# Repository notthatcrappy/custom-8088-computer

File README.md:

# custom-8088-computer
Hello everybody, in this project i try to make my own 8088 computer, it is largely based on the FE-2010A chipset and the micro8088 project by @skiselev.

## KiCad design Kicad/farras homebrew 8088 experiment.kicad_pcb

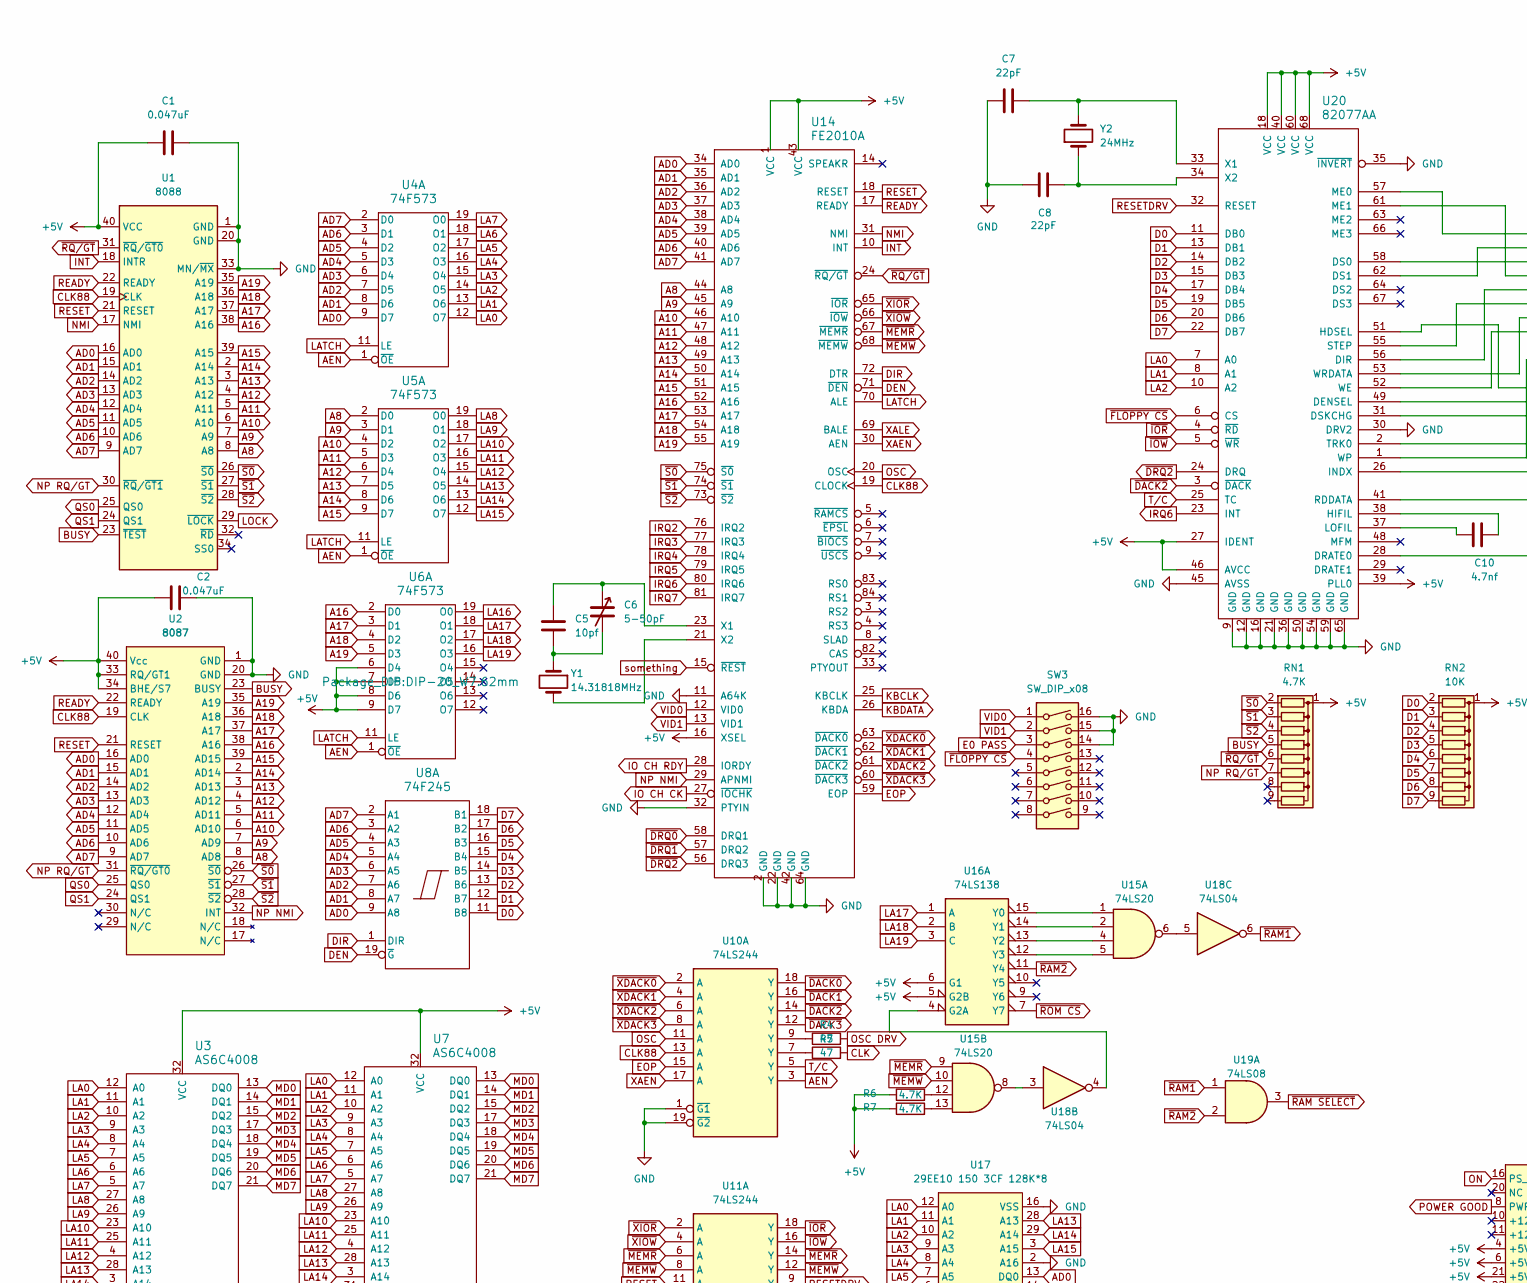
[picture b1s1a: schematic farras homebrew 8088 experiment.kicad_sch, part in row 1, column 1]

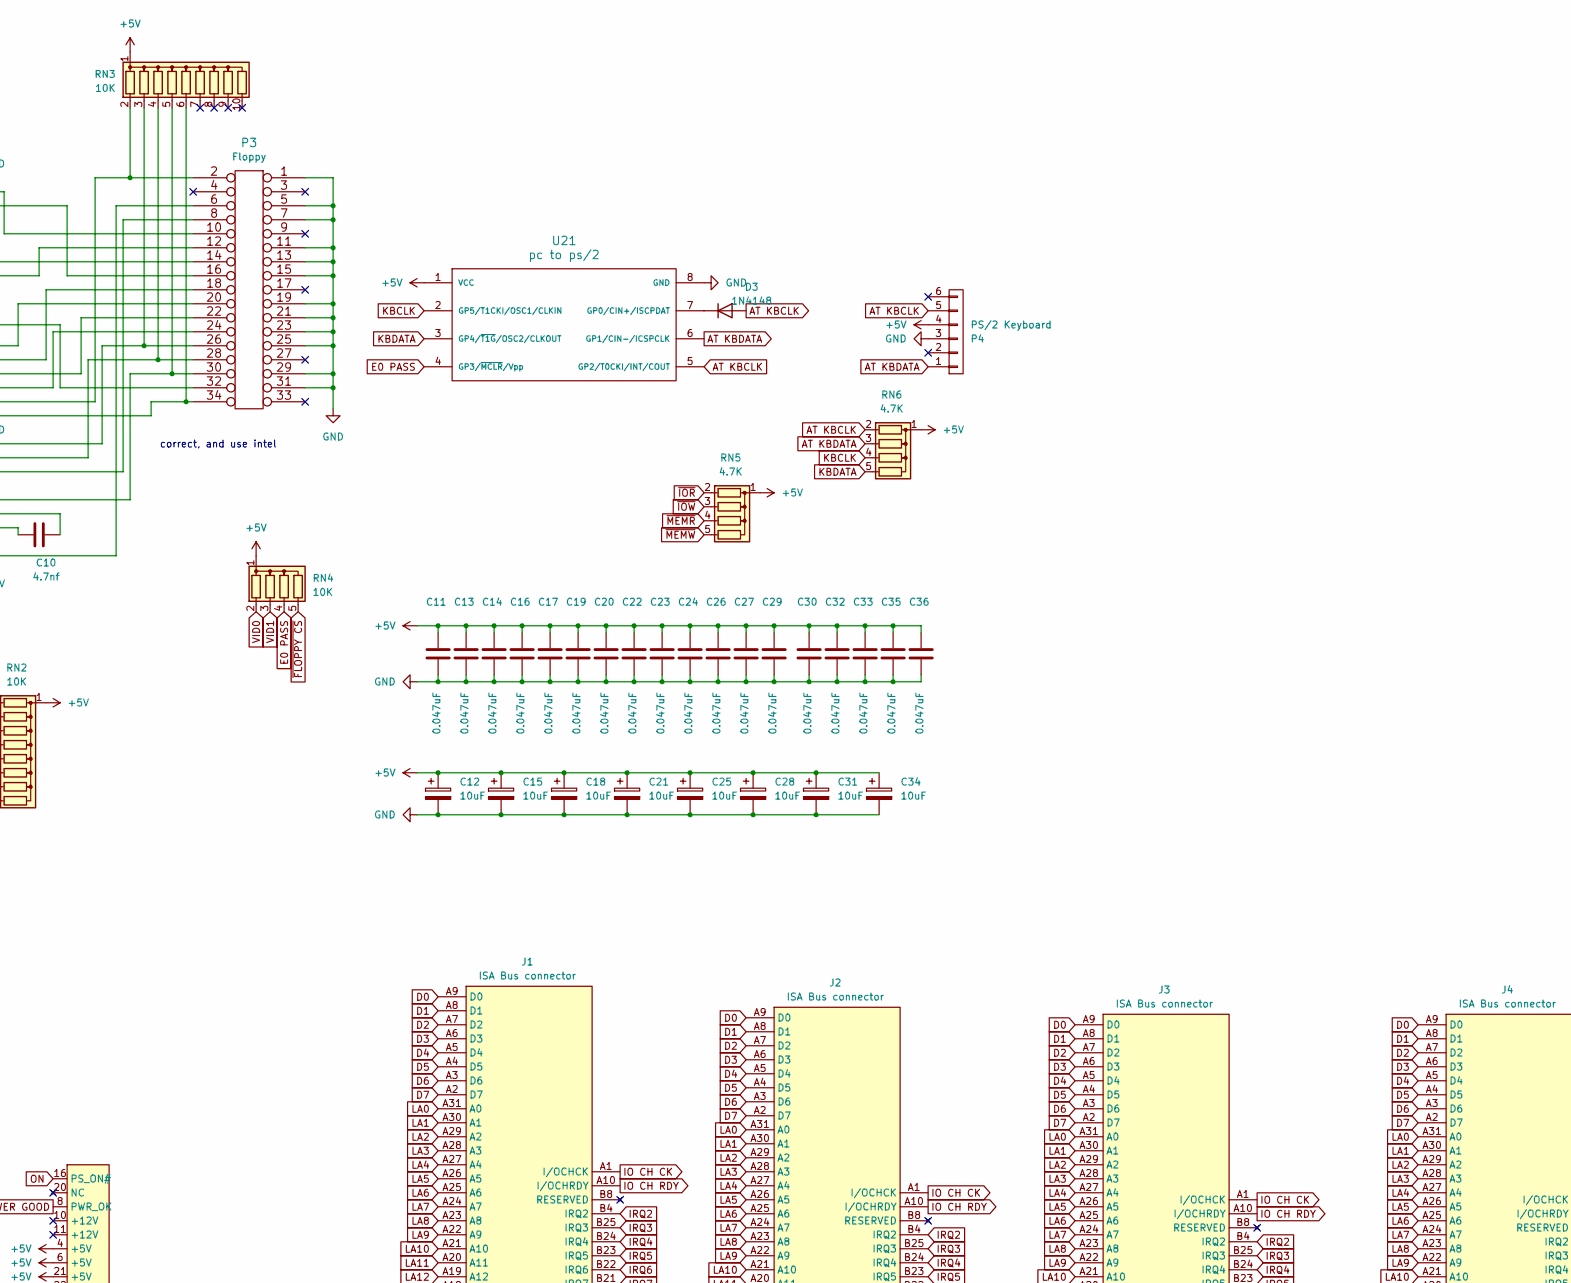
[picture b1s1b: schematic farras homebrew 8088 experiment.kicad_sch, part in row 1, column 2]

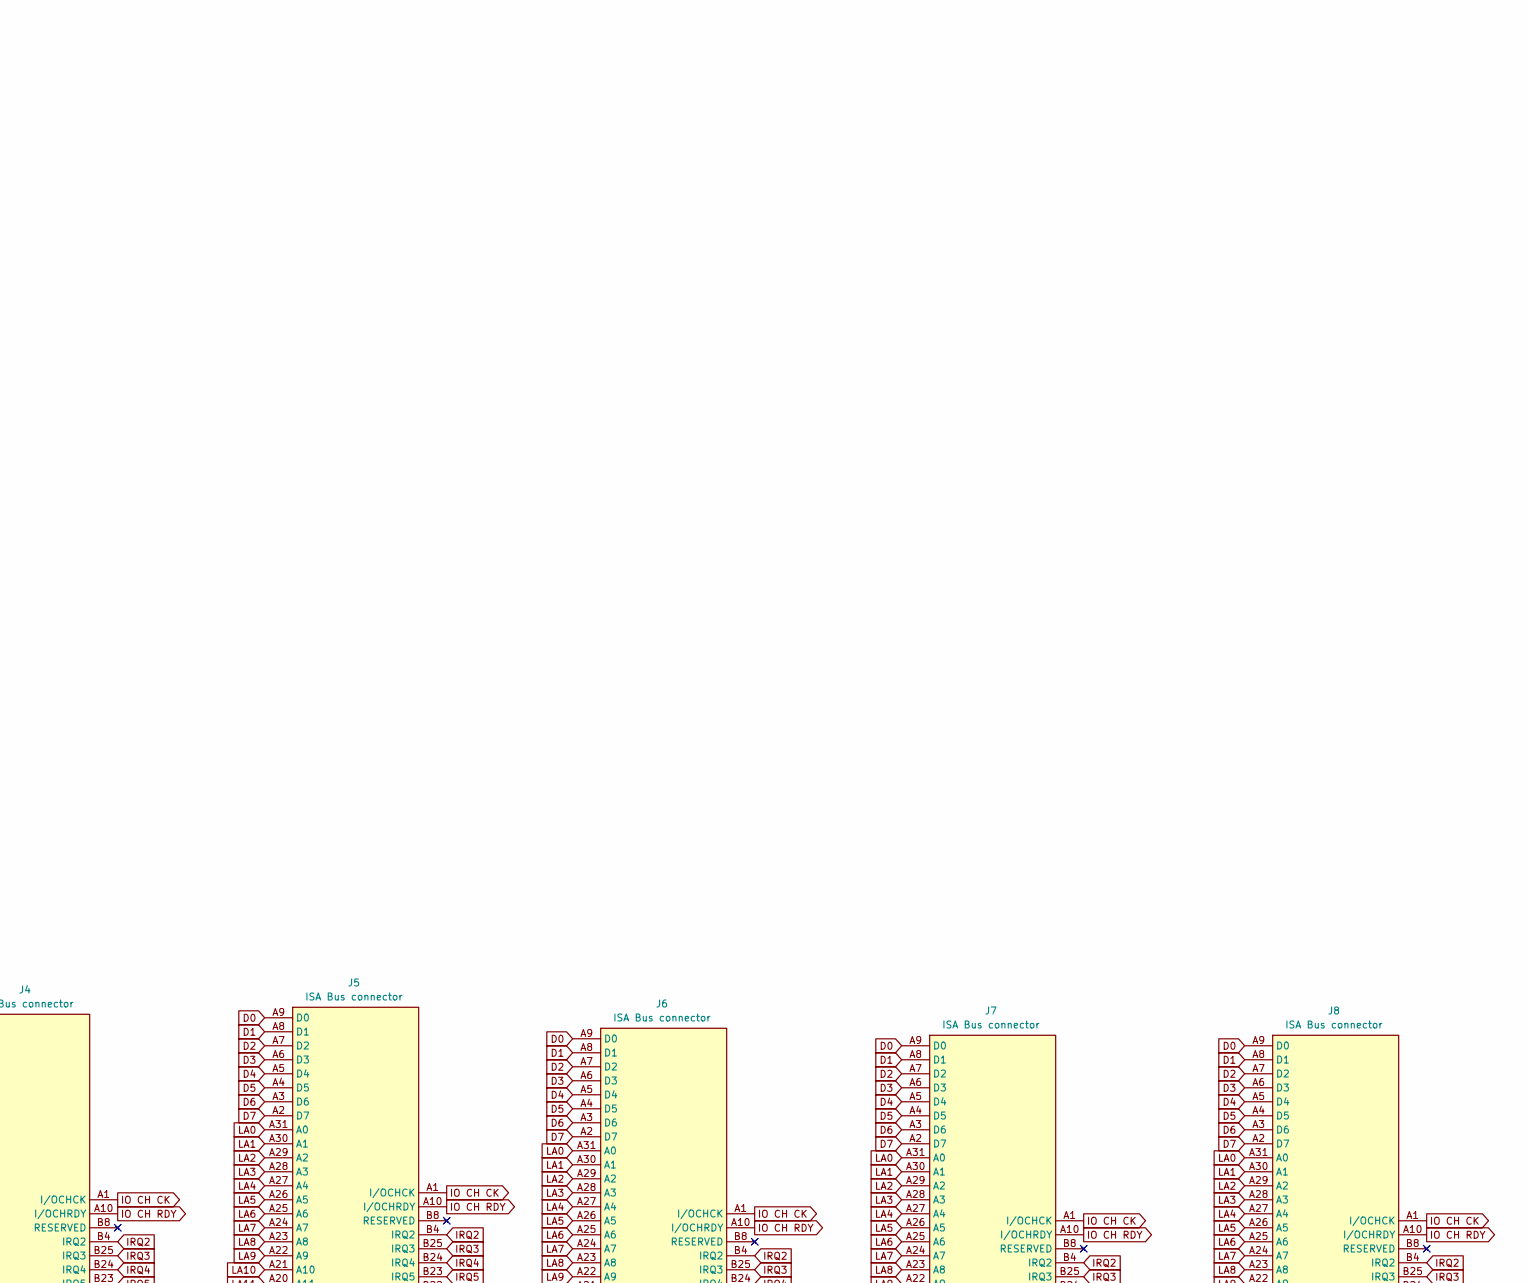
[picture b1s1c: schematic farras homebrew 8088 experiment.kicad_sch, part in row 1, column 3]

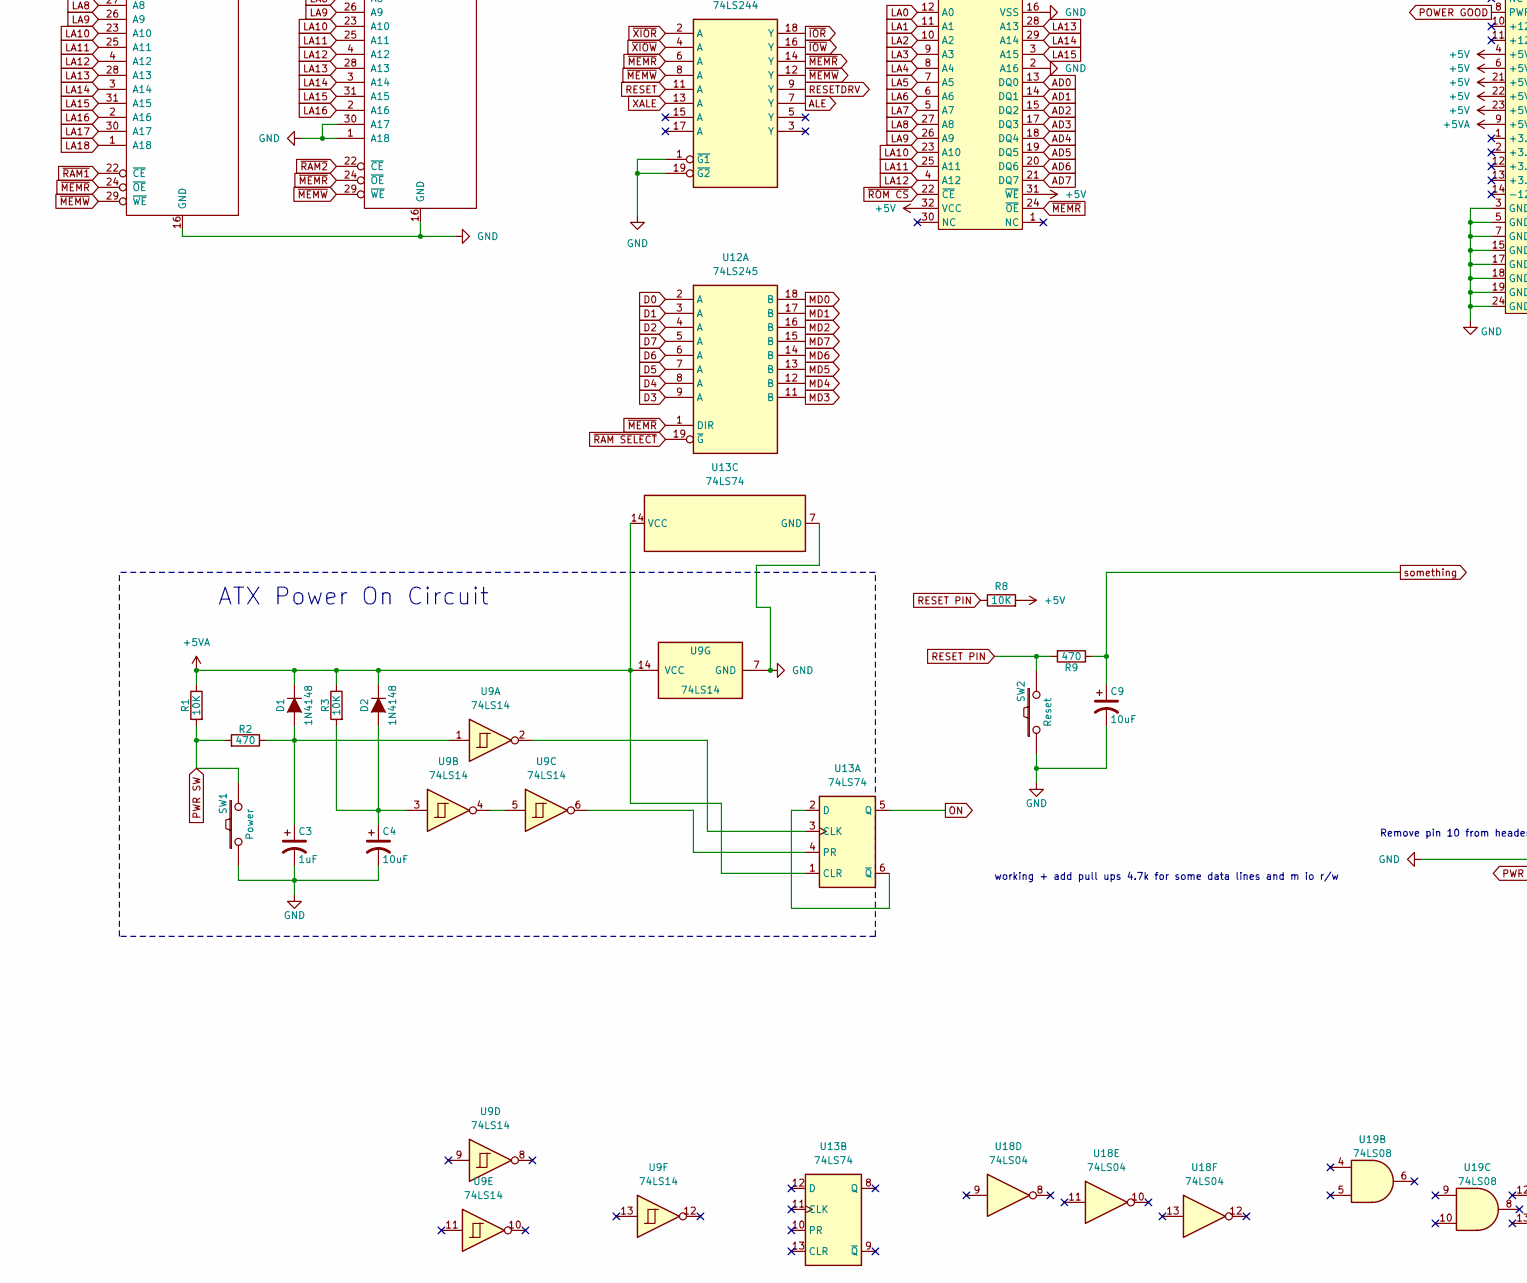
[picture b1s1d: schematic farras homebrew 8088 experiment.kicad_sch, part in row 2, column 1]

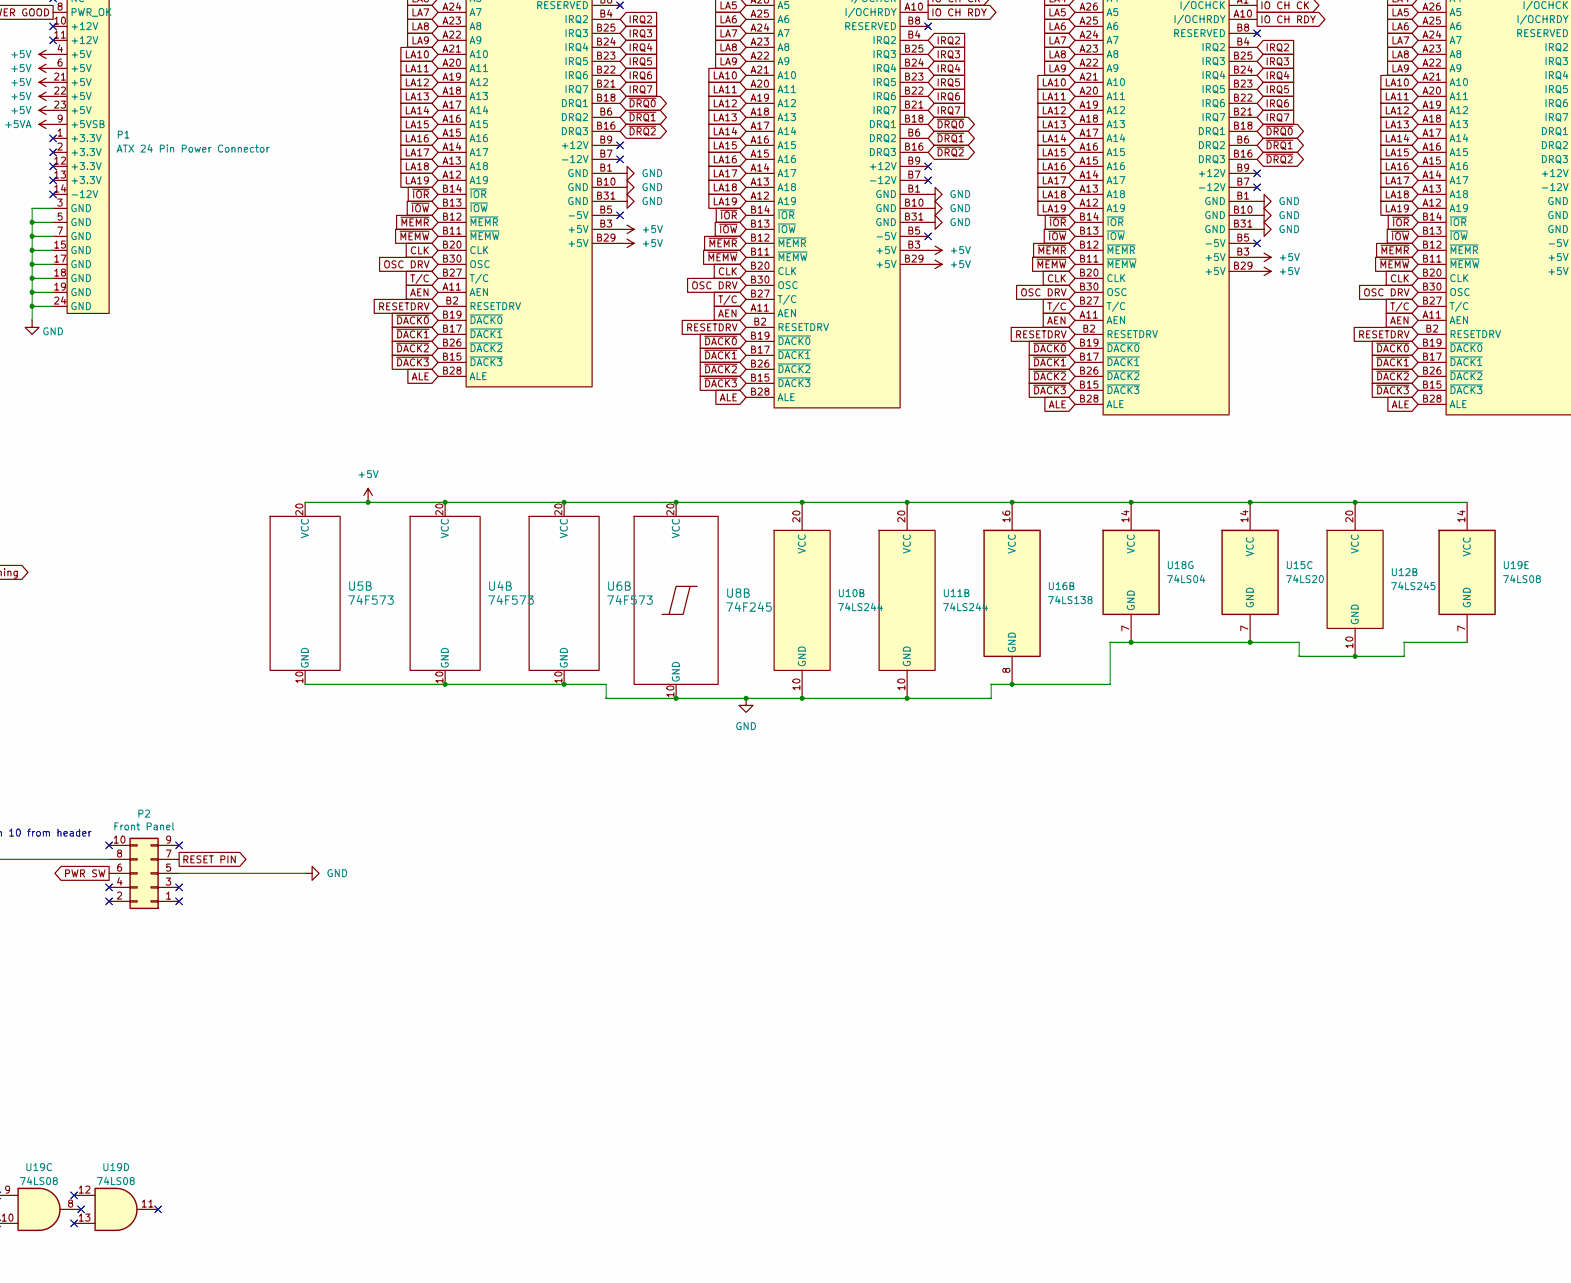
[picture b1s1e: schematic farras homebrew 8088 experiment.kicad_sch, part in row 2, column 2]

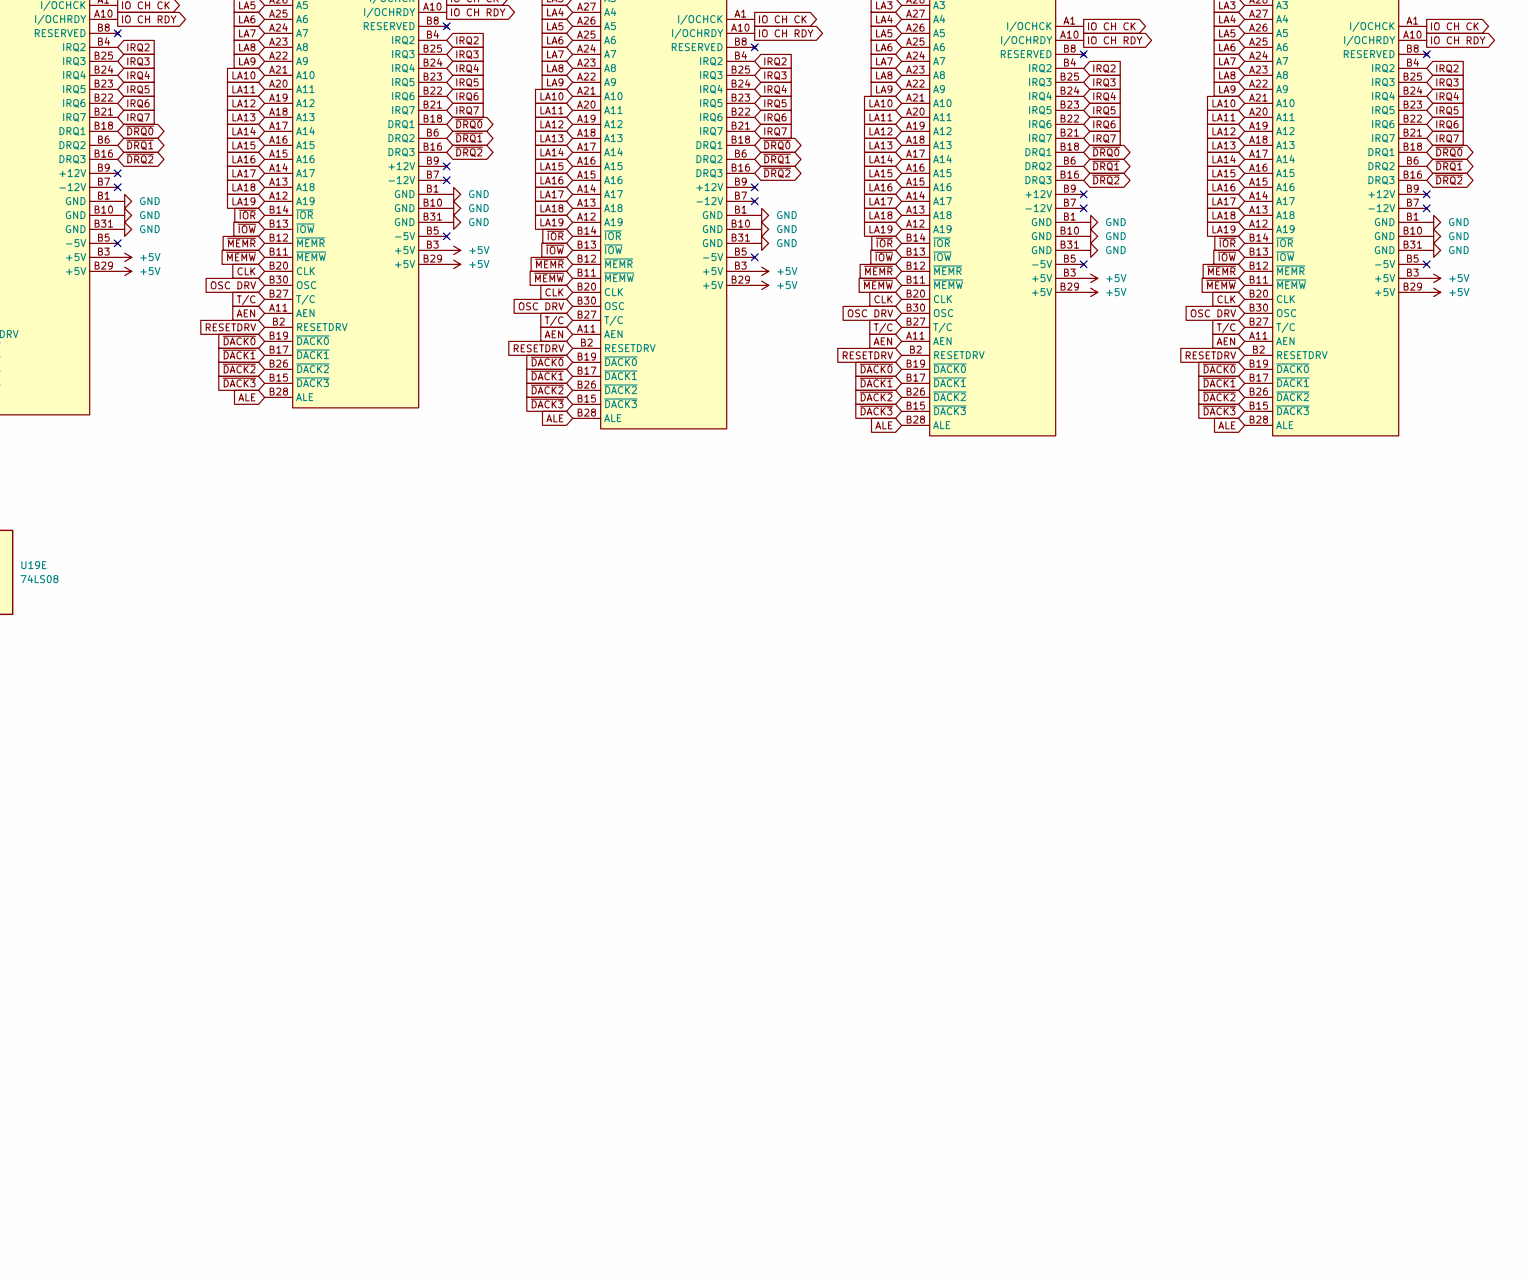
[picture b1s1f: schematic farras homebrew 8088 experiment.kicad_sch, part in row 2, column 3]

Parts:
C1, C2, C11, C13, C14, C16, C17, C19, C20, C22, C23, C24, C26, C27, C29, C30, C32, C33, C35, C36: 0.047uF; cap_unipolar
C3: 1uF; C_Disc_D4.3mm_W1.9mm_P5.00mm
C4, C9: 10uF; C_Disc_D4.3mm_W1.9mm_P5.00mm
C5: 10pf; cap_unipolar
C6: 5-50pF; trimmer cap
C7, C8: 22pF; cap_unipolar
C10: 4.7nf; cap_unipolar
C12, C15, C18, C21, C25, C28, C31, C34: 10uF; cap_tantalum_pos
D1, D2, D3: 1N4148; D_DO-34_SOD68_P7.62mm_Horizontal
J1, J2, J3, J4, J5, J6, J7, J8: ISA Bus connector; isa_edge_slot
P1: ATX 24 Pin Power Connector; Molex_Mini-Fit_Jr_5566-24A_2x12_P4.20mm_Vertical
P2: Front Panel; PinHeader_2x05_P2.54mm_Vertical
P3: Floppy; IDC-Header_2x17_P2.54mm_Vertical
P4: PS/2 Keyboard; Conn_Mini_DIN_6pin
R1, R3: 10K; R_Axial_DIN0207_L6.3mm_D2.5mm_P7.62mm_Horizontal
R2, R9: 470; R_Axial_DIN0207_L6.3mm_D2.5mm_P7.62mm_Horizontal
R4, R5: 47; resistor
R6, R7: 4.7K; resistor
R8: 10K; resistor
RN1: 4.7K; R_Array_SIP9
RN2: 10K; R_Array_SIP9
RN3: 10K; R_Array_SIP10
RN4: 10K; R_Array_SIP5
RN5, RN6: 4.7K; R_Array_SIP5
SW1: Power; SW_PUSH_6mm
SW2: Reset; SW_PUSH_6mm
SW3: SW_DIP_x08; SW_DIP_SPSTx08_Slide_9.78x22.5mm_W7.62mm_P2.54mm
U1: 8088; DIP-40_W15.24mm_Socket
U2: 8087; DIP-40_W15.24mm_Socket
U3, U7: AS6C4008; DIP-32_W15.24mm
U4, U5, U6: 74F573; DIP-20_W7.62mm
U8: 74F245; DIP-20_W7.62mm
U9: 74LS14; DIP-14_W7.62mm
U10, U11: 74LS244; DIP-20_W7.62mm
U12: 74LS245; DIP-20_W7.62mm
U13: 74LS74; DIP-14_W7.62mm_Socket
U14: FE2010A; PLCC-84_THT-Socket
U15: 74LS20; DIP-14_W7.62mm_Socket
U16: 74LS138; DIP-16_W7.62mm
U17: 29EE10 150 3CF 128K*8; DIP-32_W15.24mm_Socket
U18: 74LS04; DIP-14_W7.62mm_Socket
U19: 74LS08; DIP-14_W7.62mm_Socket
U20: 82077AA; PLCC-68_THT-Socket
U21: pc to ps/2; DIP-8_W7.62mm_Socket
Y1: 14.31818MHz; Crystal_HC49-U_Vertical
Y2: 24MHz; Crystal_HC49-U_Vertical

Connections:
+5V: C1.1, C2.1, C11.1, C12.1, C13.1, C14.1, C15.1, C16.1, C17.1, C18.1, C19.1, C20.1, C21.1, C22.1, C23.1, C24.1, C25.1, C26.1, C27.1, C28.1, C29.1, C30.1, C31.1, C32.1, C33.1, C34.1, C35.1, C36.1, J1.B3 (+5V), J1.B29 (+5V), J2.B3 (+5V), J2.B29 (+5V), J3.B3 (+5V), J3.B29 (+5V), J4.B3 (+5V), J4.B29 (+5V), J5.B3 (+5V), J5.B29 (+5V), J6.B3 (+5V), J6.B29 (+5V), J7.B3 (+5V), J7.B29 (+5V), J8.B3 (+5V), J8.B29 (+5V), P1.4 (+5V), P1.6 (+5V), P1.21 (+5V), P1.22 (+5V), P1.23 (+5V), P4.4, R6.1, R7.1, R8.2, RN1.1 (common), RN2.1 (common), RN3.1 (common), RN4.1 (common), RN5.1 (common), RN6.1 (common), U1.40 (VCC), U2.33 (RQ/GT1), U2.34 (BHE/S7), U2.40 (Vcc), U3.32 (VCC), U4.20 (VCC), U5.20 (VCC), U6.6 (D4), U6.7 (D5), U6.8 (D6), U6.9 (D7), U6.20 (VCC), U7.32 (VCC), U8.20 (VCC), U10.20 (VCC), U11.20 (VCC), U12.20 (VCC), U14.1 (VCC), U14.16 (XSEL), U14.43 (VCC), U15.14 (VCC), U16.5 (G2B), U16.6 (G1), U16.16 (VCC), U17.31 (~WE), U17.32 (VCC), U18.14 (VCC), U19.14 (VCC), U20.18 (VCC), U20.27 (IDENT), U20.39 (PLL0), U20.40 (VCC), U20.46 (AVCC), U20.60 (VCC), U20.68 (VCC), U21.1 (VCC)
+5VA: D1.1 (K), D2.1 (K), P1.9 (+5VSB), R1.1, R3.1, U9.14 (VCC), U13.1 (CLR), U13.14 (VCC)
-12V: P1.14 (-12V)
A8: U1.8 (A8), U2.8 (AD8), U5.2 (D0), U14.44 (A8)
A9: U1.7 (A9), U2.7 (AD9), U5.3 (D1), U14.45 (A9)
A10: U1.6 (A10), U2.6 (AD10), U5.4 (D2), U14.46 (A10)
A11: U1.5 (A11), U2.5 (AD11), U5.5 (D3), U14.47 (A11)
A12: U1.4 (A12), U2.4 (AD12), U5.6 (D4), U14.48 (A12)
A13: U1.3 (A13), U2.3 (AD13), U5.7 (D5), U14.49 (A13)
A14: U1.2 (A14), U2.2 (AD14), U5.8 (D6), U14.50 (A14)
A15: U1.39 (A15), U2.39 (AD15), U5.9 (D7), U14.51 (A15)
A16: U1.38 (A16), U2.38 (A16), U6.2 (D0), U14.52 (A16)
A17: U1.37 (A17), U2.37 (A17), U6.3 (D1), U14.53 (A17)
A18: U1.36 (A18), U2.36 (A18), U6.4 (D2), U14.54 (A18)
A19: U1.35 (A19), U2.35 (A19), U6.5 (D3), U14.55 (A19)
AD0: U1.16 (AD0), U2.16 (AD0), U4.9 (D7), U8.9 (A8), U14.34 (AD0), U17.13 (DQ0)
AD1: U1.15 (AD1), U2.15 (AD1), U4.8 (D6), U8.8 (A7), U14.35 (AD1), U17.14 (DQ1)
AD2: U1.14 (AD2), U2.14 (AD2), U4.7 (D5), U8.7 (A6), U14.36 (AD2), U17.15 (DQ2)
AD3: U1.13 (AD3), U2.13 (AD3), U4.6 (D4), U8.6 (A5), U14.37 (AD3), U17.17 (DQ3)
AD4: U1.12 (AD4), U2.12 (AD4), U4.5 (D3), U8.5 (A4), U14.38 (AD4), U17.18 (DQ4)
AD5: U1.11 (AD5), U2.11 (AD5), U4.4 (D2), U8.4 (A3), U14.39 (AD5), U17.19 (DQ5)
AD6: U1.10 (AD6), U2.10 (AD6), U4.3 (D1), U8.3 (A2), U14.40 (AD6), U17.20 (DQ6)
AD7: U1.9 (AD7), U2.9 (AD7), U4.2 (D0), U8.2 (A1), U14.41 (AD7), U17.21 (DQ7)
AEN: J1.A11 (AEN), J2.A11 (AEN), J3.A11 (AEN), J4.A11 (AEN), J5.A11 (AEN), J6.A11 (AEN), J7.A11 (AEN), J8.A11 (AEN), U4.1 (~OE), U5.1 (~OE), U6.1 (~OE), U10.3 (Y)
ALE: J1.B28 (ALE), J2.B28 (ALE), J3.B28 (ALE), J4.B28 (ALE), J5.B28 (ALE), J6.B28 (ALE), J7.B28 (ALE), J8.B28 (ALE), U11.7 (Y)
AT KBCLK: D3.2 (A), P4.5, RN6.2 (R1), U21.5 (GP2/T0CKI/INT/COUT)
AT KBDATA: P4.1, RN6.3 (R2), U21.6 (GP1/CIN-/ICSPCLK)
BUSY: RN1.5 (R4), U1.23 (~TEST), U2.23 (BUSY)
CLK: J1.B20 (CLK), J2.B20 (CLK), J3.B20 (CLK), J4.B20 (CLK), J5.B20 (CLK), J6.B20 (CLK), J7.B20 (CLK), J8.B20 (CLK), R5.2
CLK88: U1.19 (CLK), U2.19 (CLK), U10.13 (A), U14.19 (CLOCK)
D0: J1.A9 (D0), J2.A9 (D0), J3.A9 (D0), J4.A9 (D0), J5.A9 (D0), J6.A9 (D0), J7.A9 (D0), J8.A9 (D0), RN2.2 (R1), U8.11 (B8), U12.2 (A), U20.11 (DB0)
D1: J1.A8 (D1), J2.A8 (D1), J3.A8 (D1), J4.A8 (D1), J5.A8 (D1), J6.A8 (D1), J7.A8 (D1), J8.A8 (D1), RN2.3 (R2), U8.12 (B7), U12.3 (A), U20.13 (DB1)
D2: J1.A7 (D2), J2.A7 (D2), J3.A7 (D2), J4.A7 (D2), J5.A7 (D2), J6.A7 (D2), J7.A7 (D2), J8.A7 (D2), RN2.4 (R3), U8.13 (B6), U12.4 (A), U20.14 (DB2)
D3: J1.A6 (D3), J2.A6 (D3), J3.A6 (D3), J4.A6 (D3), J5.A6 (D3), J6.A6 (D3), J7.A6 (D3), J8.A6 (D3), RN2.5 (R4), U8.14 (B5), U12.9 (A), U20.15 (DB3)
D4: J1.A5 (D4), J2.A5 (D4), J3.A5 (D4), J4.A5 (D4), J5.A5 (D4), J6.A5 (D4), J7.A5 (D4), J8.A5 (D4), RN2.6 (R5), U8.15 (B4), U12.8 (A), U20.17 (DB4)
D5: J1.A4 (D5), J2.A4 (D5), J3.A4 (D5), J4.A4 (D5), J5.A4 (D5), J6.A4 (D5), J7.A4 (D5), J8.A4 (D5), RN2.7 (R6), U8.16 (B3), U12.7 (A), U20.19 (DB5)
D6: J1.A3 (D6), J2.A3 (D6), J3.A3 (D6), J4.A3 (D6), J5.A3 (D6), J6.A3 (D6), J7.A3 (D6), J8.A3 (D6), RN2.8 (R7), U8.17 (B2), U12.6 (A), U20.20 (DB6)
D7: J1.A2 (D7), J2.A2 (D7), J3.A2 (D7), J4.A2 (D7), J5.A2 (D7), J6.A2 (D7), J7.A2 (D7), J8.A2 (D7), RN2.9 (R8), U8.18 (B1), U12.5 (A), U20.22 (DB7)
DEN: U8.19 (~G), U14.71 (~DEN)
DIR: U8.1 (DIR), U14.72 (DTR)
E0 PASS: RN4.4 (R3), SW3.3, U21.4 (GP3/~MCLR/Vpp)
EOP: U10.15 (A), U14.59 (EOP)
GND: C1.2, C2.2, C3.2, C4.2, C7.1, C8.1, C9.2, C11.2, C12.2, C13.2, C14.2, C15.2, C16.2, C17.2, C18.2, C19.2, C20.2, C21.2, C22.2, C23.2, C24.2, C25.2, C26.2, C27.2, C28.2, C29.2, C30.2, C31.2, C32.2, C33.2, C34.2, C35.2, C36.2, J1.B1 (GND), J1.B10 (GND), J1.B31 (GND), J2.B1 (GND), J2.B10 (GND), J2.B31 (GND), J3.B1 (GND), J3.B10 (GND), J3.B31 (GND), J4.B1 (GND), J4.B10 (GND), J4.B31 (GND), J5.B1 (GND), J5.B10 (GND), J5.B31 (GND), J6.B1 (GND), J6.B10 (GND), J6.B31 (GND), J7.B1 (GND), J7.B10 (GND), J7.B31 (GND), J8.B1 (GND), J8.B10 (GND), J8.B31 (GND), P1.3 (GND), P1.5 (GND), P1.7 (GND), P1.15 (GND), P1.17 (GND), P1.18 (GND), P1.19 (GND), P1.24 (GND), P2.5, P2.8, P3.1, P3.5, P3.7, P3.11, P3.13, P3.15, P3.19, P3.21, P3.23, P3.25, P3.29, P3.31, P4.3, SW1.1, SW2.1, SW3.14, SW3.15, SW3.16, U1.1 (GND), U1.20 (GND), U1.33 (MN/~MX), U2.1 (GND), U2.20 (GND), U3.16 (GND), U4.10 (GND), U5.10 (GND), U6.10 (GND), U7.1 (A18), U7.16 (GND), U7.30 (A17), U8.10 (GND), U9.7 (GND), U10.1 (~G1), U10.10 (GND), U10.19 (~G2), U11.1 (~G1), U11.10 (GND), U11.19 (~G2), U12.10 (GND), U13.7 (GND), U14.2 (GND), U14.11 (A64K), U14.22 (GND), U14.32 (PTYIN), U14.42 (GND), U14.64 (GND)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
INT: U1.18 (INTR), U14.10 (INT)
IO CH CK: J1.A1 (I/OCHCK), J2.A1 (I/OCHCK), J3.A1 (I/OCHCK), J4.A1 (I/OCHCK), J5.A1 (I/OCHCK), J6.A1 (I/OCHCK), J7.A1 (I/OCHCK), J8.A1 (I/OCHCK), U14.27 (~IOCHK)
IO CH RDY: J1.A10 (I/OCHRDY), J2.A10 (I/OCHRDY), J3.A10 (I/OCHRDY), J4.A10 (I/OCHRDY), J5.A10 (I/OCHRDY), J6.A10 (I/OCHRDY), J7.A10 (I/OCHRDY), J8.A10 (I/OCHRDY), U14.28 (IORDY)
IRQ2: J1.B4 (IRQ2), J2.B4 (IRQ2), J3.B4 (IRQ2), J4.B4 (IRQ2), J5.B4 (IRQ2), J6.B4 (IRQ2), J7.B4 (IRQ2), J8.B4 (IRQ2), U14.76 (IRQ2)
IRQ3: J1.B25 (IRQ3), J2.B25 (IRQ3), J3.B25 (IRQ3), J4.B25 (IRQ3), J5.B25 (IRQ3), J6.B25 (IRQ3), J7.B25 (IRQ3), J8.B25 (IRQ3), U14.77 (IRQ3)
IRQ4: J1.B24 (IRQ4), J2.B24 (IRQ4), J3.B24 (IRQ4), J4.B24 (IRQ4), J5.B24 (IRQ4), J6.B24 (IRQ4), J7.B24 (IRQ4), J8.B24 (IRQ4), U14.78 (IRQ4)
IRQ5: J1.B23 (IRQ5), J2.B23 (IRQ5), J3.B23 (IRQ5), J4.B23 (IRQ5), J5.B23 (IRQ5), J6.B23 (IRQ5), J7.B23 (IRQ5), J8.B23 (IRQ5), U14.79 (IRQ5)
IRQ6: J1.B22 (IRQ6), J2.B22 (IRQ6), J3.B22 (IRQ6), J4.B22 (IRQ6), J5.B22 (IRQ6), J6.B22 (IRQ6), J7.B22 (IRQ6), J8.B22 (IRQ6), U14.80 (IRQ6), U20.23 (INT)
IRQ7: J1.B21 (IRQ7), J2.B21 (IRQ7), J3.B21 (IRQ7), J4.B21 (IRQ7), J5.B21 (IRQ7), J6.B21 (IRQ7), J7.B21 (IRQ7), J8.B21 (IRQ7), U14.81 (IRQ7)
KBCLK: RN6.4 (R3), U14.25 (KBCLK), U21.2 (GP5/T1CKI/OSC1/CLKIN)
KBDATA: RN6.5 (R4), U14.26 (KBDA), U21.3 (GP4/~T1G/OSC2/CLKOUT)
LA0: J1.A31 (A0), J2.A31 (A0), J3.A31 (A0), J4.A31 (A0), J5.A31 (A0), J6.A31 (A0), J7.A31 (A0), J8.A31 (A0), U3.12 (A0), U4.12 (O7), U7.12 (A0), U17.12 (A0), U20.7 (A0)
LA1: J1.A30 (A1), J2.A30 (A1), J3.A30 (A1), J4.A30 (A1), J5.A30 (A1), J6.A30 (A1), J7.A30 (A1), J8.A30 (A1), U3.11 (A1), U4.13 (O6), U7.11 (A1), U17.11 (A1), U20.8 (A1)
LA2: J1.A29 (A2), J2.A29 (A2), J3.A29 (A2), J4.A29 (A2), J5.A29 (A2), J6.A29 (A2), J7.A29 (A2), J8.A29 (A2), U3.10 (A2), U4.14 (O5), U7.10 (A2), U17.10 (A2), U20.10 (A2)
LA3: J1.A28 (A3), J2.A28 (A3), J3.A28 (A3), J4.A28 (A3), J5.A28 (A3), J6.A28 (A3), J7.A28 (A3), J8.A28 (A3), U3.9 (A3), U4.15 (O4), U7.9 (A3), U17.9 (A3)
LA4: J1.A27 (A4), J2.A27 (A4), J3.A27 (A4), J4.A27 (A4), J5.A27 (A4), J6.A27 (A4), J7.A27 (A4), J8.A27 (A4), U3.8 (A4), U4.16 (O3), U7.8 (A4), U17.8 (A4)
LA5: J1.A26 (A5), J2.A26 (A5), J3.A26 (A5), J4.A26 (A5), J5.A26 (A5), J6.A26 (A5), J7.A26 (A5), J8.A26 (A5), U3.7 (A5), U4.17 (O2), U7.7 (A5), U17.7 (A5)
LA6: J1.A25 (A6), J2.A25 (A6), J3.A25 (A6), J4.A25 (A6), J5.A25 (A6), J6.A25 (A6), J7.A25 (A6), J8.A25 (A6), U3.6 (A6), U4.18 (O1), U7.6 (A6), U17.6 (A6)
LA7: J1.A24 (A7), J2.A24 (A7), J3.A24 (A7), J4.A24 (A7), J5.A24 (A7), J6.A24 (A7), J7.A24 (A7), J8.A24 (A7), U3.5 (A7), U4.19 (O0), U7.5 (A7), U17.5 (A7)
LA8: J1.A23 (A8), J2.A23 (A8), J3.A23 (A8), J4.A23 (A8), J5.A23 (A8), J6.A23 (A8), J7.A23 (A8), J8.A23 (A8), U3.27 (A8), U5.19 (O0), U7.27 (A8), U17.27 (A8)
LA9: J1.A22 (A9), J2.A22 (A9), J3.A22 (A9), J4.A22 (A9), J5.A22 (A9), J6.A22 (A9), J7.A22 (A9), J8.A22 (A9), U3.26 (A9), U5.18 (O1), U7.26 (A9), U17.26 (A9)
LA10: J1.A21 (A10), J2.A21 (A10), J3.A21 (A10), J4.A21 (A10), J5.A21 (A10), J6.A21 (A10), J7.A21 (A10), J8.A21 (A10), U3.23 (A10), U5.17 (O2), U7.23 (A10), U17.23 (A10)
LA11: J1.A20 (A11), J2.A20 (A11), J3.A20 (A11), J4.A20 (A11), J5.A20 (A11), J6.A20 (A11), J7.A20 (A11), J8.A20 (A11), U3.25 (A11), U5.16 (O3), U7.25 (A11), U17.25 (A11)
LA12: J1.A19 (A12), J2.A19 (A12), J3.A19 (A12), J4.A19 (A12), J5.A19 (A12), J6.A19 (A12), J7.A19 (A12), J8.A19 (A12), U3.4 (A12), U5.15 (O4), U7.4 (A12), U17.4 (A12)
LA13: J1.A18 (A13), J2.A18 (A13), J3.A18 (A13), J4.A18 (A13), J5.A18 (A13), J6.A18 (A13), J7.A18 (A13), J8.A18 (A13), U3.28 (A13), U5.14 (O5), U7.28 (A13), U17.28 (A13)
LA14: J1.A17 (A14), J2.A17 (A14), J3.A17 (A14), J4.A17 (A14), J5.A17 (A14), J6.A17 (A14), J7.A17 (A14), J8.A17 (A14), U3.3 (A14), U5.13 (O6), U7.3 (A14), U17.29 (A14)
LA15: J1.A16 (A15), J2.A16 (A15), J3.A16 (A15), J4.A16 (A15), J5.A16 (A15), J6.A16 (A15), J7.A16 (A15), J8.A16 (A15), U3.31 (A15), U5.12 (O7), U7.31 (A15), U17.3 (A15)
LA16: J1.A15 (A16), J2.A15 (A16), J3.A15 (A16), J4.A15 (A16), J5.A15 (A16), J6.A15 (A16), J7.A15 (A16), J8.A15 (A16), U3.2 (A16), U6.19 (O0), U7.2 (A16)
LA17: J1.A14 (A17), J2.A14 (A17), J3.A14 (A17), J4.A14 (A17), J5.A14 (A17), J6.A14 (A17), J7.A14 (A17), J8.A14 (A17), U3.30 (A17), U6.18 (O1), U16.1 (A)
LA18: J1.A13 (A18), J2.A13 (A18), J3.A13 (A18), J4.A13 (A18), J5.A13 (A18), J6.A13 (A18), J7.A13 (A18), J8.A13 (A18), U3.1 (A18), U6.17 (O2), U16.2 (B)
LA19: J1.A12 (A19), J2.A12 (A19), J3.A12 (A19), J4.A12 (A19), J5.A12 (A19), J6.A12 (A19), J7.A12 (A19), J8.A12 (A19), U6.16 (O3), U16.3 (C)
LATCH: U4.11 (LE), U5.11 (LE), U6.11 (LE), U14.70 (ALE)
LOCK: U1.29 (~LOCK)
MD0: U3.13 (DQ0), U7.13 (DQ0), U12.18 (B)
MD1: U3.14 (DQ1), U7.14 (DQ1), U12.17 (B)
MD2: U3.15 (DQ2), U7.15 (DQ2), U12.16 (B)
MD3: U3.17 (DQ3), U7.17 (DQ3), U12.11 (B)
MD4: U3.18 (DQ4), U7.18 (DQ4), U12.12 (B)
MD5: U3.19 (DQ5), U7.19 (DQ5), U12.13 (B)
MD6: U3.20 (DQ6), U7.20 (DQ6), U12.14 (B)
MD7: U3.21 (DQ7), U7.21 (DQ7), U12.15 (B)
NMI: U1.17 (NMI), U14.31 (NMI)
NP NMI: U2.32 (INT), U14.29 (APNMI)
NP RQ/GT: RN1.7 (R6), U1.30 (~RQ/~GT1), U2.31 (~RQ/GT0)
unnamed: C5.2, C6.2, Y1.1
unnamed: C3.1, D1.2 (A), R2.1, U9.1
unnamed: C4.1, D2.2 (A), R3.2, U9.3
unnamed: D3.1 (K), U21.7 (GP0/CIN+/ISCPDAT)
unnamed: P3.2, RN3.2 (R1), U20.49 (DENSEL)
unnamed: P3.6, U20.28 (DRATE0)
unnamed: P3.8, U20.26 (INDX)
unnamed: P3.10, U20.57 (ME0)
unnamed: P3.12, U20.62 (DS1)
unnamed: P3.14, U20.58 (DS0)
unnamed: P3.16, U20.61 (ME1)
unnamed: P3.18, U20.56 (DIR)
unnamed: P3.20, U20.55 (STEP)
unnamed: P3.22, U20.53 (WRDATA)
unnamed: P3.24, U20.52 (WE)
unnamed: P3.26, RN3.3 (R2), U20.2 (TRK0)
unnamed: P3.28, RN3.4 (R3), U20.1 (WP)
unnamed: P3.30, RN3.5 (R4), U20.41 (RDDATA)
unnamed: P3.32, U20.51 (HDSEL)
unnamed: P3.34, RN3.6 (R5), U20.31 (DSKCHG)
unnamed: R4.1, U10.9 (Y)
unnamed: R5.1, U10.7 (Y)
unnamed: R6.2, U15.12
unnamed: R7.2, U15.13
unnamed: U9.4, U9.5
unnamed: U9.2, U13.3 (CLK)
unnamed: U13.2 (D), U13.6 (~Q)
unnamed: U9.6, U13.4 (PR)
unnamed: C5.1, C6.1, U14.23 (X1)
unnamed: U14.21 (X2), Y1.2
unnamed: U15.6, U18.5
unnamed: U15.8, U18.3
unnamed: U16.4 (G2A), U18.4
unnamed: U15.1, U16.15 (Y0)
unnamed: U15.2, U16.14 (Y1)
unnamed: U15.4, U16.13 (Y2)
unnamed: U15.5, U16.12 (Y3)
unnamed: C10.2, U20.38 (HIFIL)
unnamed: C10.1, U20.37 (LOFIL)
unnamed: C7.2, U20.33 (X1), Y2.2
unnamed: C8.2, U20.34 (X2), Y2.1
ON: P1.16 (PS_ON#), U13.5 (Q)
OSC: U10.11 (A), U14.20 (OSC)
OSC DRV: J1.B30 (OSC), J2.B30 (OSC), J3.B30 (OSC), J4.B30 (OSC), J5.B30 (OSC), J6.B30 (OSC), J7.B30 (OSC), J8.B30 (OSC), R4.2
POWER GOOD: P1.8 (PWR_OK)
PWR SW: P2.6, R1.2, R2.2, SW1.2
QS0: U1.25 (QS0), U2.25 (QS0)
QS1: U1.24 (QS1), U2.24 (QS1)
READY: U1.22 (READY), U2.22 (READY), U14.17 (READY)
RESET: U1.21 (RESET), U2.21 (RESET), U11.11 (A), U14.18 (RESET)
RESET PIN: P2.7, R8.1, R9.2, SW2.2
RESETDRV: J1.B2 (RESETDRV), J2.B2 (RESETDRV), J3.B2 (RESETDRV), J4.B2 (RESETDRV), J5.B2 (RESETDRV), J6.B2 (RESETDRV), J7.B2 (RESETDRV), J8.B2 (RESETDRV), U11.9 (Y), U20.32 (RESET)
T/C: J1.B27 (T/C), J2.B27 (T/C), J3.B27 (T/C), J4.B27 (T/C), J5.B27 (T/C), J6.B27 (T/C), J7.B27 (T/C), J8.B27 (T/C), U10.5 (Y), U20.25 (TC)
VID0: RN4.2 (R1), SW3.1, U14.12 (VID0)
VID1: RN4.3 (R2), SW3.2, U14.13 (VID1)
XAEN: U10.17 (A), U14.30 (AEN)
XALE: U11.13 (A), U14.69 (BALE)
something: C9.1, R9.1, U14.15 (~REST)
~DACK0: J1.B19 (~DACK0), J2.B19 (~DACK0), J3.B19 (~DACK0), J4.B19 (~DACK0), J5.B19 (~DACK0), J6.B19 (~DACK0), J7.B19 (~DACK0), J8.B19 (~DACK0), U10.18 (Y)
~DACK1: J1.B17 (~DACK1), J2.B17 (~DACK1), J3.B17 (~DACK1), J4.B17 (~DACK1), J5.B17 (~DACK1), J6.B17 (~DACK1), J7.B17 (~DACK1), J8.B17 (~DACK1), U10.16 (Y)
~DACK2: J1.B26 (~DACK2), J2.B26 (~DACK2), J3.B26 (~DACK2), J4.B26 (~DACK2), J5.B26 (~DACK2), J6.B26 (~DACK2), J7.B26 (~DACK2), J8.B26 (~DACK2), U10.14 (Y), U20.3 (~DACK)
~DACK3: J1.B15 (~DACK3), J2.B15 (~DACK3), J3.B15 (~DACK3), J4.B15 (~DACK3), J5.B15 (~DACK3), J6.B15 (~DACK3), J7.B15 (~DACK3), J8.B15 (~DACK3), U10.12 (Y)
~DRQ0: J1.B18 (DRQ1), J2.B18 (DRQ1), J3.B18 (DRQ1), J4.B18 (DRQ1), J5.B18 (DRQ1), J6.B18 (DRQ1), J7.B18 (DRQ1), J8.B18 (DRQ1), U14.58 (DRQ1)
~DRQ1: J1.B6 (DRQ2), J2.B6 (DRQ2), J3.B6 (DRQ2), J4.B6 (DRQ2), J5.B6 (DRQ2), J6.B6 (DRQ2), J7.B6 (DRQ2), J8.B6 (DRQ2), U14.57 (DRQ2)
~DRQ2: J1.B16 (DRQ3), J2.B16 (DRQ3), J3.B16 (DRQ3), J4.B16 (DRQ3), J5.B16 (DRQ3), J6.B16 (DRQ3), J7.B16 (DRQ3), J8.B16 (DRQ3), U14.56 (DRQ3), U20.24 (DRQ)
~FLOPPY CS: RN4.5 (R4), SW3.4, U20.6 (CS)
~IOR: J1.B14 (~IOR), J2.B14 (~IOR), J3.B14 (~IOR), J4.B14 (~IOR), J5.B14 (~IOR), J6.B14 (~IOR), J7.B14 (~IOR), J8.B14 (~IOR), RN5.2 (R1), U11.18 (Y), U20.4 (~RD)
~IOW: J1.B13 (~IOW), J2.B13 (~IOW), J3.B13 (~IOW), J4.B13 (~IOW), J5.B13 (~IOW), J6.B13 (~IOW), J7.B13 (~IOW), J8.B13 (~IOW), RN5.3 (R2), U11.16 (Y), U20.5 (~WR)
~MEMR: J1.B12 (~MEMR), J2.B12 (~MEMR), J3.B12 (~MEMR), J4.B12 (~MEMR), J5.B12 (~MEMR), J6.B12 (~MEMR), J7.B12 (~MEMR), J8.B12 (~MEMR), RN5.4 (R3), U3.24 (~OE), U7.24 (~OE), U11.6 (A), U11.14 (Y), U12.1 (DIR), U14.67 (~MEMR), U15.9, U17.24 (~OE)
~MEMW: J1.B11 (~MEMW), J2.B11 (~MEMW), J3.B11 (~MEMW), J4.B11 (~MEMW), J5.B11 (~MEMW), J6.B11 (~MEMW), J7.B11 (~MEMW), J8.B11 (~MEMW), RN5.5 (R4), U3.29 (~WE), U7.29 (~WE), U11.8 (A), U11.12 (Y), U14.68 (~MEMW), U15.10
~RAM1: U3.22 (~CE), U18.6, U19.1
~RAM2: U7.22 (~CE), U16.11 (Y4), U19.2
~RAM SELECT: U12.19 (~G), U19.3
~ROM CS: U16.7 (Y7), U17.22 (~CE)
~RQ/GT: RN1.6 (R5), U1.31 (~RQ/~GT0), U14.24 (~RQ/GT)
~S0: RN1.2 (R1), U1.26 (~S0), U2.26 (~S0), U14.75 (~S0)
~S1: RN1.3 (R2), U1.27 (~S1), U2.27 (~S1), U14.74 (~S1)
~S2: RN1.4 (R3), U1.28 (~S2), U2.28 (~S2), U14.73 (~S2)
~XDACK0: U10.2 (A), U14.63 (~DACK0)
~XDACK1: U10.4 (A), U14.62 (~DACK1)
~XDACK2: U10.6 (A), U14.61 (~DACK2)
~XDACK3: U10.8 (A), U14.60 (~DACK3)
~XIOR: U11.2 (A), U14.65 (~IOR)
~XIOW: U11.4 (A), U14.66 (~IOW)

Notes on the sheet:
Remove pin 10 from header
ATX Power On Circuit
correct, and use intel
working + add pull ups 4.7k for some data lines and m io r/w

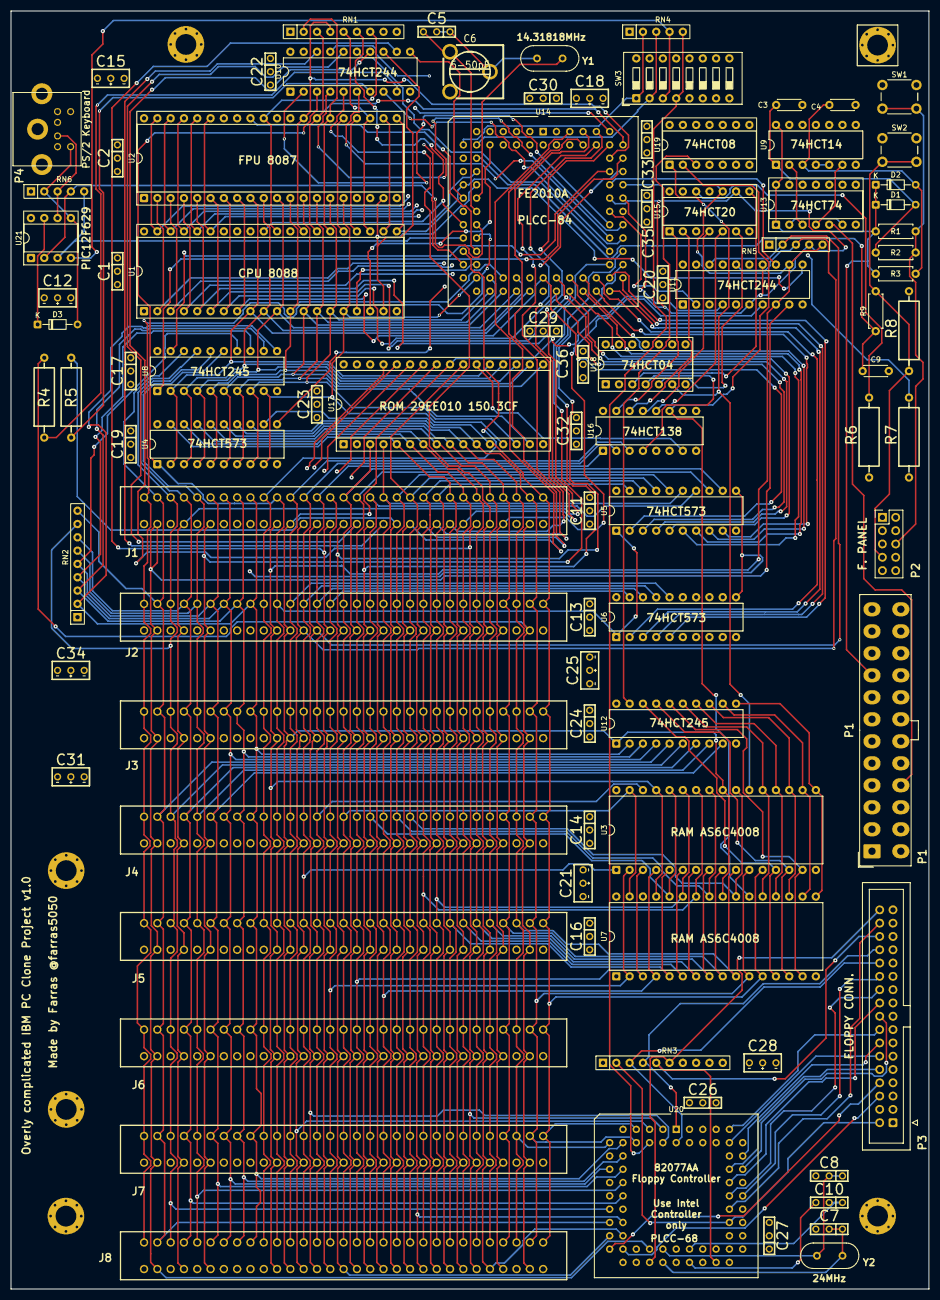
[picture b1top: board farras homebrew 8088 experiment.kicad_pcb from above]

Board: 4 copper layers, 175.3 x 244.0 mm, 92 parts (0 on the bottom side), 168 nets.
